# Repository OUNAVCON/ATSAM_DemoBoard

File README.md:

# ATSAM_DemoBoard
Demo board for use with 48-LQFP ATSAMC21 and ATSAMD21 MCU's

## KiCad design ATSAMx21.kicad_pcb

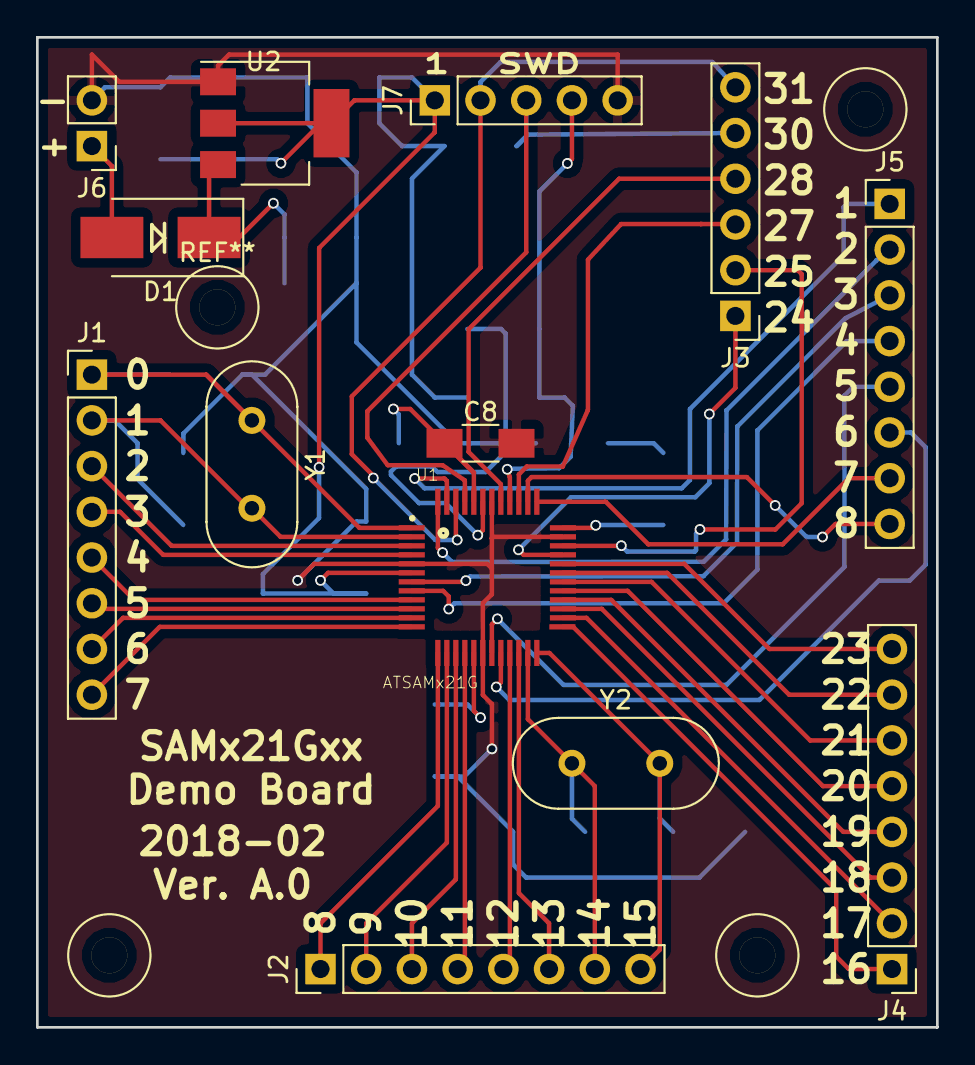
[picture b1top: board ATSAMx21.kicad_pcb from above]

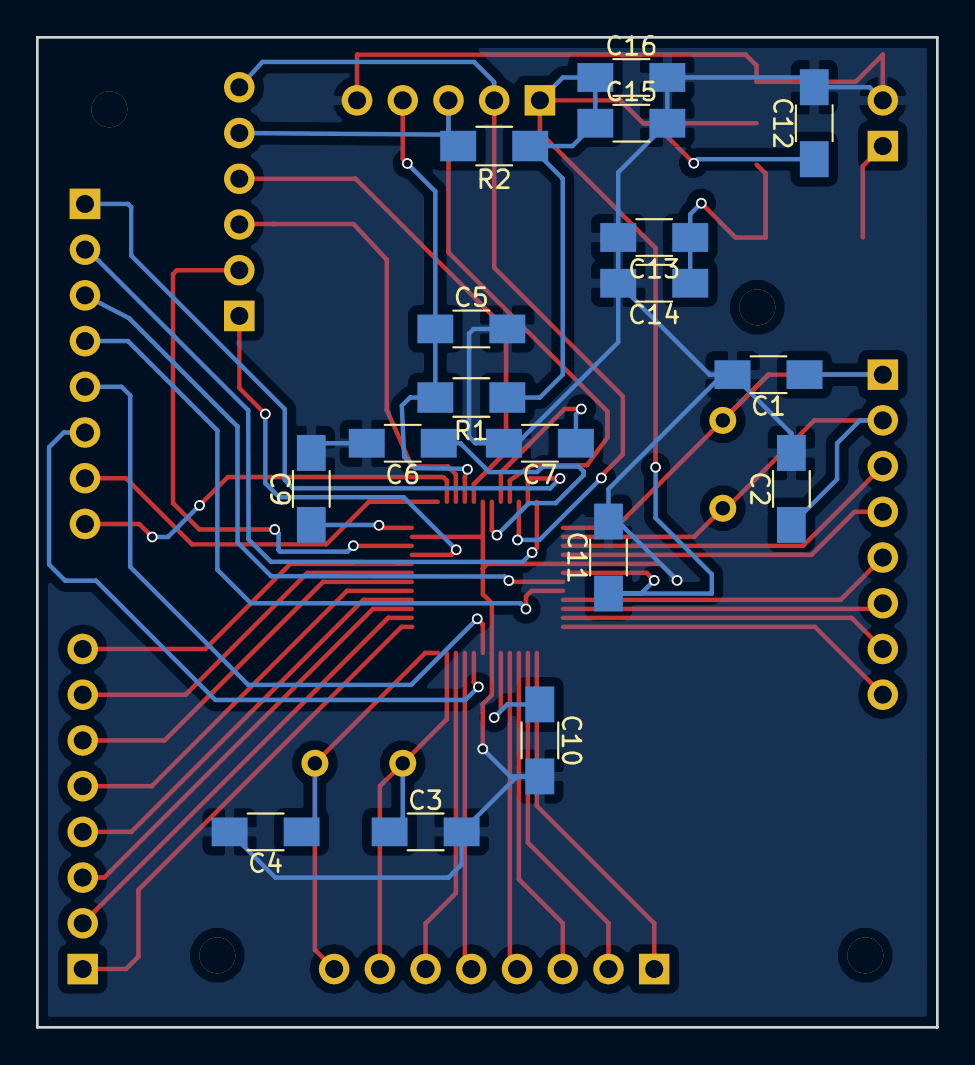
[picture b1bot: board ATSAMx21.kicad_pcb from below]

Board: 2 copper layers, 50.0 x 55.0 mm, 30 parts (17 on the bottom side), 47 nets.

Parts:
C1, C2, C3, C4: 22pF; C_1206_HandSoldering
C5: 1uF; C_1206_HandSoldering
C6: 1uFC; C_1206_HandSoldering
C7, C11: 100nF-Close; C_1206_HandSoldering
C8, C12, C14, C15: 10uF; C_1206_HandSoldering
C9, C10, C13, C16: 100nF; C_1206_HandSoldering
D1: 1N4001; D_SMB_Handsoldering
J1: PORTA_1; Pin_Header_Straight_1x08_Pitch2.54mm
J2: PORTA_2; Pin_Header_Straight_1x08_Pitch2.54mm
J3: PORTA_4; Pin_Header_Straight_1x06_Pitch2.54mm
J4: PORTA_3; Pin_Header_Straight_1x08_Pitch2.54mm
J5: PORTB; Pin_Header_Straight_1x08_Pitch2.54mm
J6: PWR; Pin_Header_Straight_1x02_Pitch2.54mm
J7: JTAG; Pin_Header_Straight_1x05_Pitch2.54mm
R1: 10k; R_1206_HandSoldering
R2: 1k; R_1206_HandSoldering
U1: ATSAMx21G; QFP50P900X900X120-48N
U2: AP111733; SOT-223
Y1: XOSC32K; Crystal_HC49-4H_Vertical
Y2: XOSC; Crystal_HC49-4H_Vertical

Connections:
/MCU/PA0: C1.1, J1.1, U1.1, Y1.1
/MCU/PA1: C2.1, J1.2, U1.2, Y1.2
/MCU/PA2: J1.3, U1.3
/MCU/PA3: J1.4, U1.4
/MCU/PA4: J1.5, U1.9
/MCU/PA5: J1.6, U1.10
/MCU/PA6: J1.7, U1.11
/MCU/PA7: J1.8, U1.12
/MCU/PA8: J2.1, U1.13
/MCU/PA9: J2.2, U1.14
/MCU/PA10: J2.3, U1.15
/MCU/PA11: J2.4, U1.16
/MCU/PA12: J2.5, U1.21
/MCU/PA13: J2.6, U1.22
/MCU/PA14: C3.1, J2.7, U1.23, Y2.1
/MCU/PA15: C4.1, J2.8, U1.24, Y2.2
/MCU/PA16: J4.1, U1.25
/MCU/PA17: J4.2, U1.26
/MCU/PA18: J4.3, U1.27
/MCU/PA19: J4.4, U1.28
/MCU/PA20: J4.5, U1.29
/MCU/PA21: J4.6, U1.30
/MCU/PA22: J4.7, U1.31
/MCU/PA23: J4.8, U1.32
/MCU/PA24: J3.1, U1.33
/MCU/PA25: J3.2, U1.34
/MCU/PA27: J3.3, U1.39
/MCU/PA28: J3.4, U1.41
GND: C1.2, C2.2, C3.2, C4.2, C5.2, C6.2, C7.2, C8.2, C9.2, C10.2, C11.2, C12.2, C13.2, C14.2, C15.2, C16.2, J6.2, J7.5, U1.5, U1.18, U1.35, U1.42, U2.1
unnamed: C6.1, U1.43
unnamed: C7.1, C8.1, U1.44
unnamed: C9.1, U1.36
unnamed: C10.1, U1.17
unnamed: C13.1, C14.1, D1.1, U2.3
unnamed: D1.2, J6.1
unnamed: J5.1, U1.47
unnamed: J5.2, U1.48
unnamed: J5.3, U1.7
unnamed: J5.4, U1.8
unnamed: J5.5, U1.19
unnamed: J5.6, U1.20
unnamed: J5.7, U1.37
unnamed: J5.8, U1.38
RESET: C5.1, J7.4, R1.2, U1.40
SWDCLK: J3.5, J7.3, R2.2, U1.45
SWDIO: J3.6, J7.2, U1.46
VDD: C11.1, C12.1, C15.1, C16.1, J7.1, R1.1, R2.1, U1.6, U2.2, U2.4

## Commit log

2018-02-14 Added external oscillators and updated SWD pull up
2018-02-17 Updated Schematic and Created Laytout
2018-02-19 Added Gerbers
2018-03-02 Generated gerbers
